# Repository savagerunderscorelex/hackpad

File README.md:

# LoveBoard

The LoveBoard is a 4-key macro pad with an OLED display. I made it to easily access shortcuts I use frequently (copy, paste, cut, delete).

I created the macropad with only 4 keys just because I'm a beginner at PCB design (if I were a bit more experienced, I would've designed the PCB with more keys lol; it was a struggle just to add 4 :cry:), but I'm happy with how it turned out so far!

## Photos

### Schematic

### PCB Design

### Case

### Full Assembly

The case was designed in AutoDesk! Deeper learning curve compared to Onshape (what I'm used to).

## Bill of Materials

- 4x Cherry MX Switches
- 128x32 OLED Display
- 4x Cherry DSA Keycaps
- 1x Seeed Studio XIAO RP2040

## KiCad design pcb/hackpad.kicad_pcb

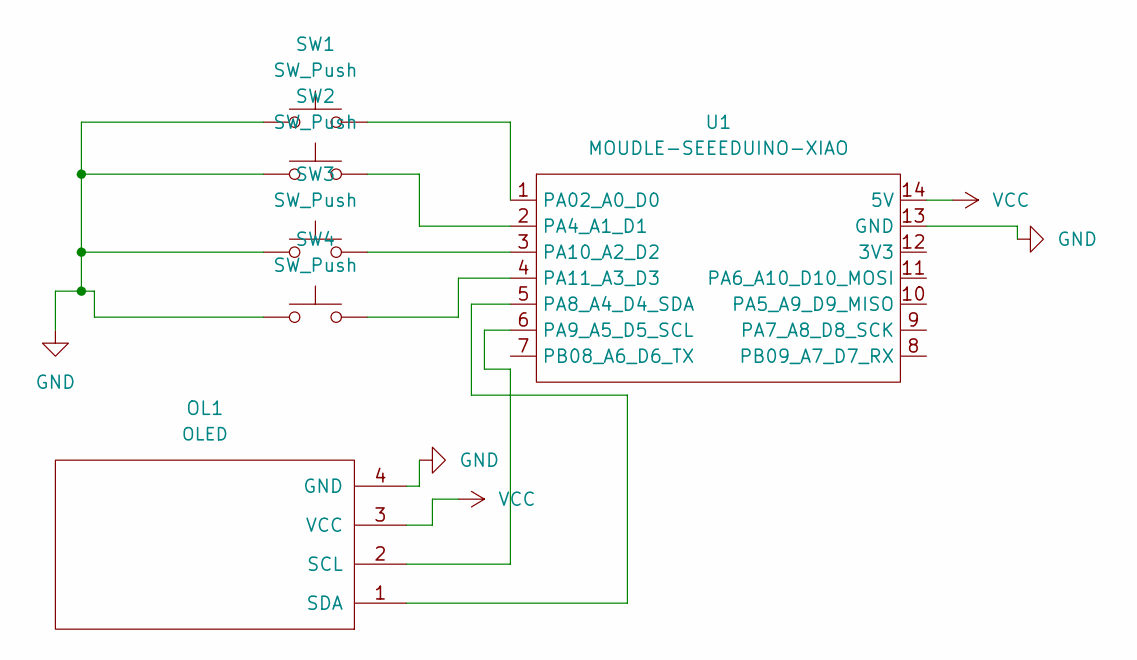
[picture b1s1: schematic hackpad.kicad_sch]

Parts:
OL1: OLED; SSD1306-0.91-OLED-4pin-128x32
SW1, SW2, SW3, SW4: SW_Push; SW_Cherry_MX_1.00u_PCB
U1: MOUDLE-SEEEDUINO-XIAO; XIAO-Generic-Hybrid-14P-2.54-21X17.8MM

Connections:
GND: OL1.4 (GND), SW1.1, SW2.1, SW3.1, SW4.1, U1.13 (GND)
unnamed: OL1.2 (SCL), U1.6 (PA9_A5_D5_SCL)
unnamed: OL1.1 (SDA), U1.5 (PA8_A4_D4_SDA)
unnamed: SW1.2, U1.1 (PA02_A0_D0)
unnamed: SW2.2, U1.2 (PA4_A1_D1)
unnamed: SW3.2, U1.3 (PA10_A2_D2)
unnamed: SW4.2, U1.4 (PA11_A3_D3)
VCC: OL1.3 (VCC), U1.14 (5V)

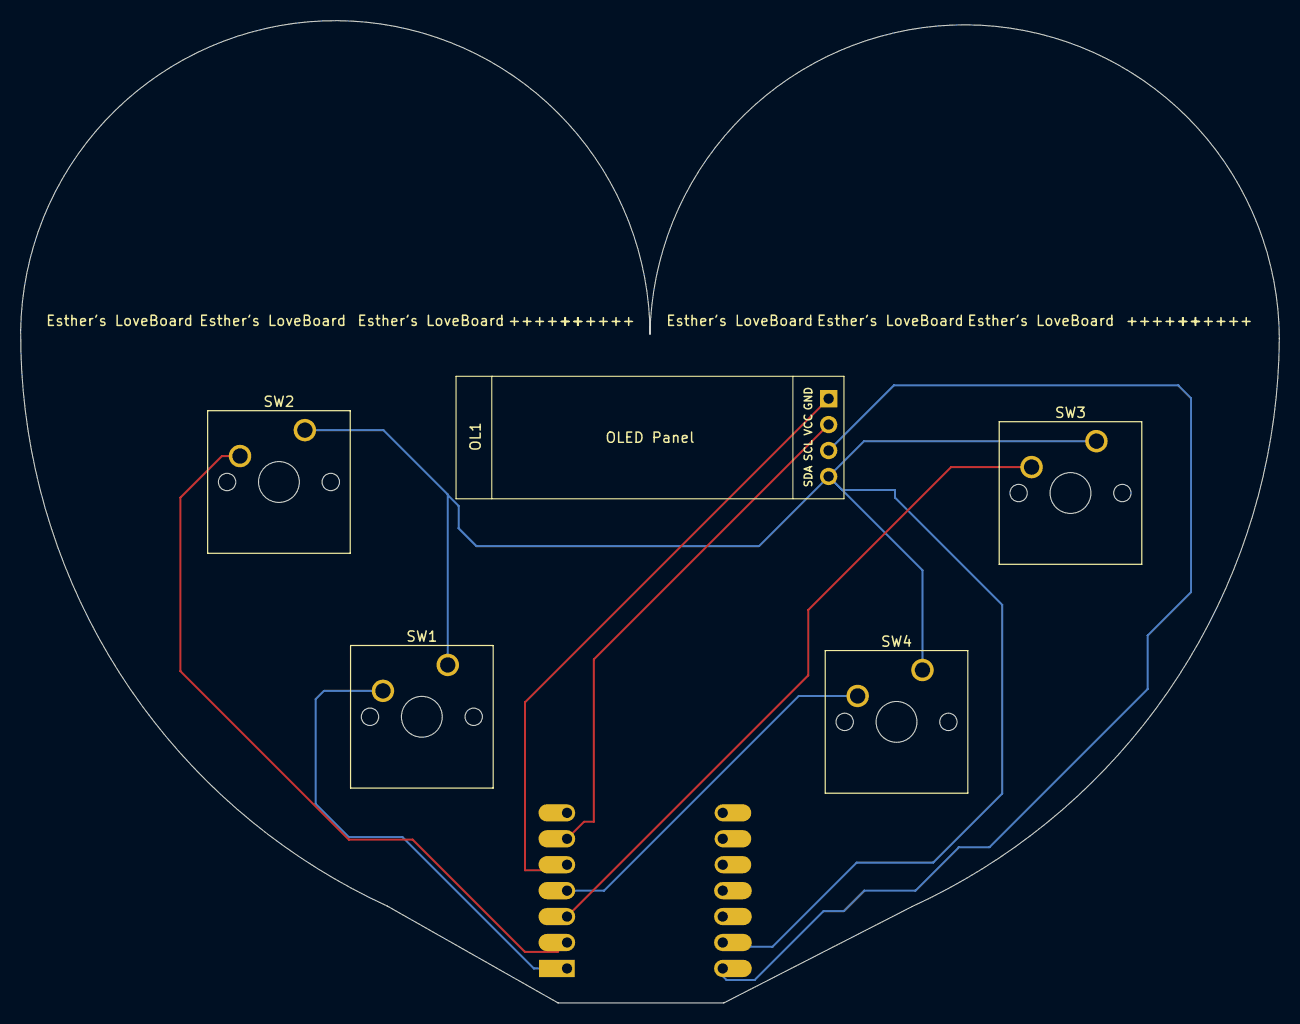
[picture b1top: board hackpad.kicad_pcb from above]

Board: 2 copper layers, 123.3 x 96.2 mm, 6 parts (1 on the bottom side), 8 nets.
